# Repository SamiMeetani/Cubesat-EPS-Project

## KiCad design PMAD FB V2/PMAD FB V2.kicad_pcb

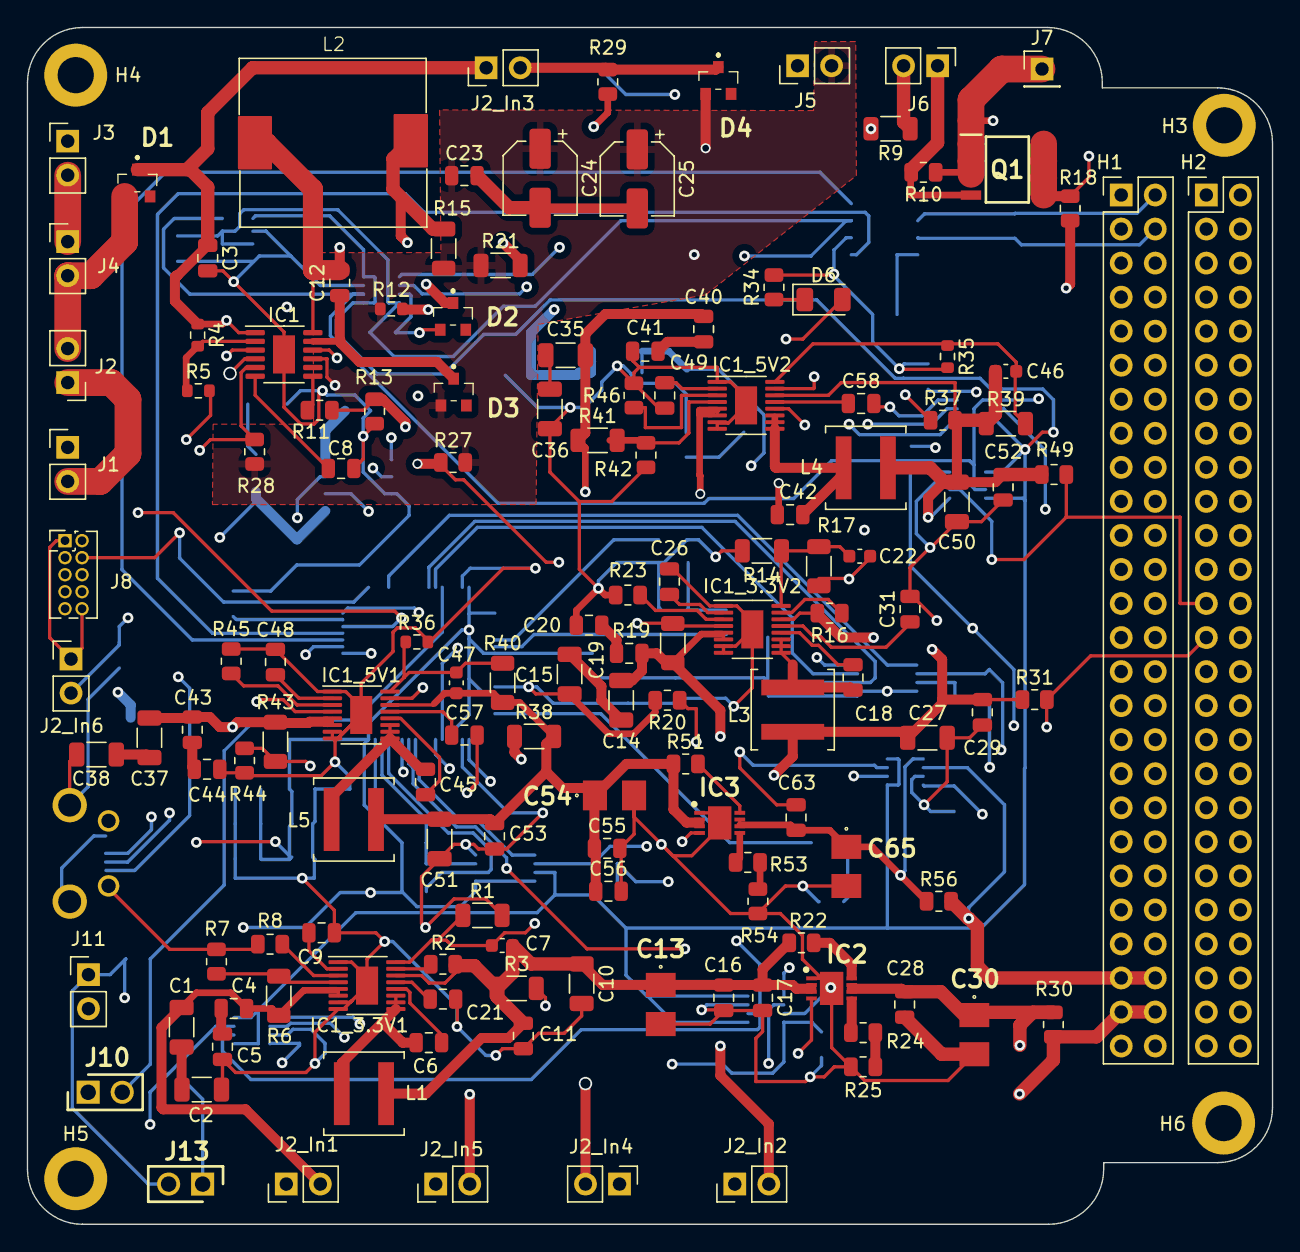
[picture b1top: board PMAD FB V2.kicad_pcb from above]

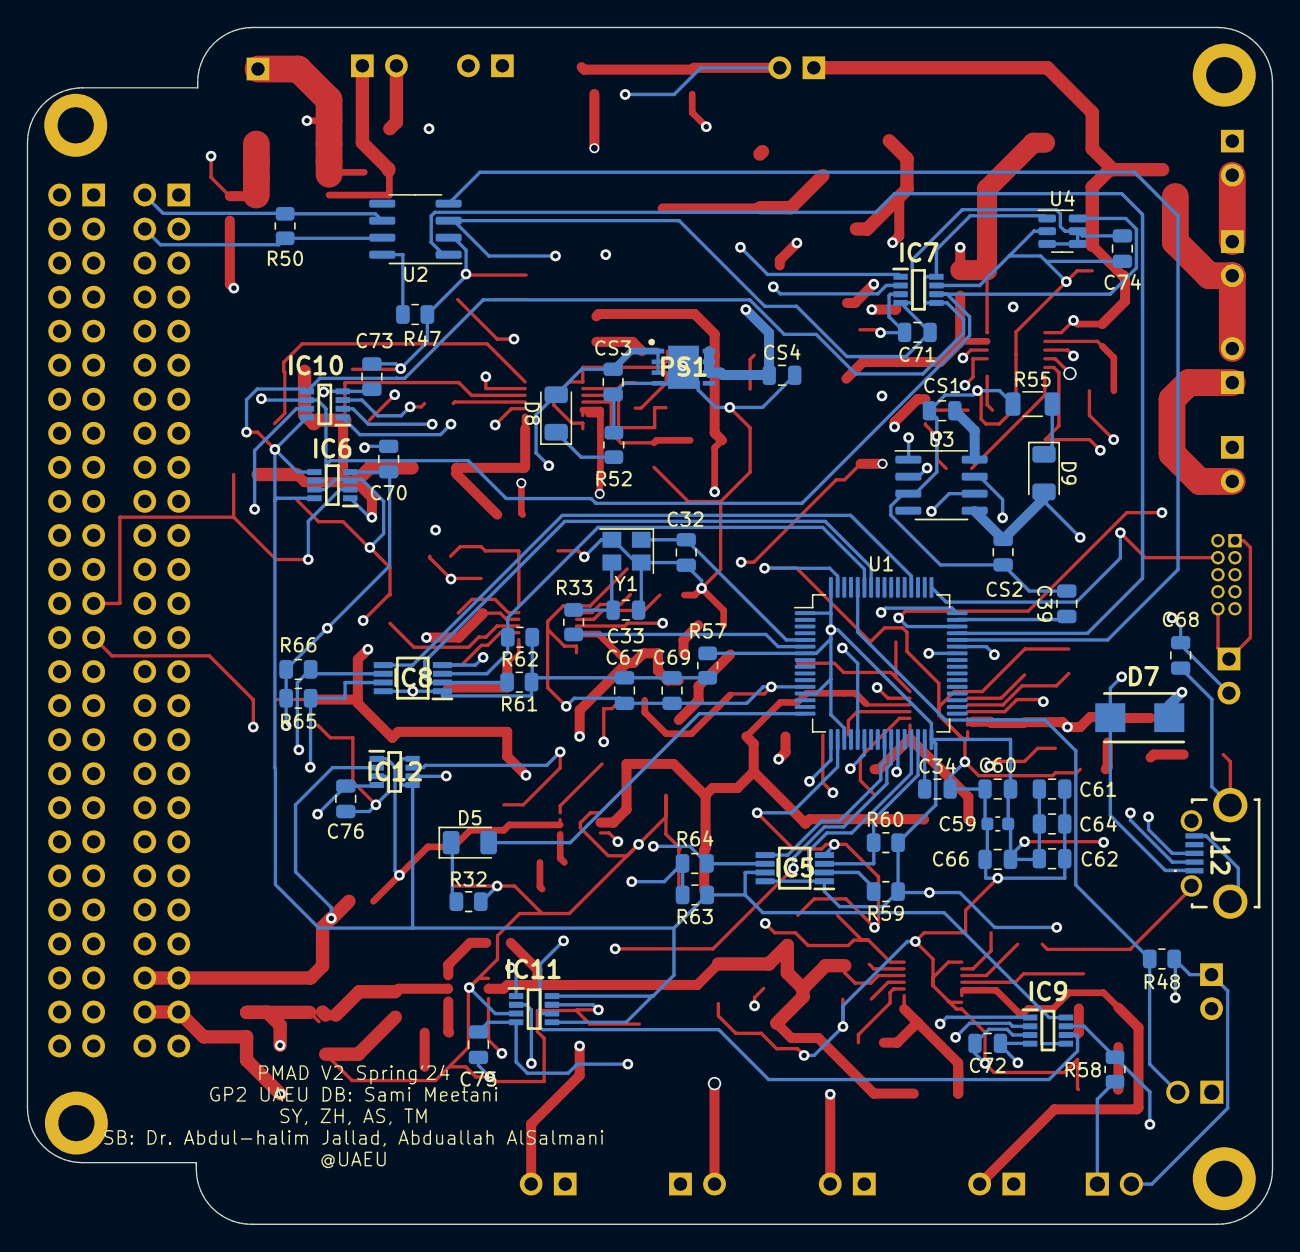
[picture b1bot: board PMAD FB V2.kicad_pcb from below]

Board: 4 copper layers, 92.9 x 89.3 mm, 205 parts (60 on the bottom side), 123 nets.

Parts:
C1, C2, C14, C15, C35, C36, C37, C38: 4.7uF; C_1206_3216Metric
C3, C23: 10uF; C_0805_2012Metric
C4, C5, C6, C9, C18, C19, C20, C26, C40, C41, C42, C43, C44, C45, C48, C49: 0.1uF; C_0805_2012Metric
C7, C22, C46, C47: 4.7pF; C_0603_1608Metric
C8, C11, C12, C21, C29, C31, C52, C53, C57, C58: 1uF; C_0805_2012Metric
C10, C27, C50, C51: 47uF; C_1206_3216Metric
C13, C30, C54, C65: T490B157M010ATE500; T490B
C16, C55: 10u; C_0805_2012Metric
C17, C28, C56, C63: 0.1u; C_0805_2012Metric
C24, C25: 47uF; CP_Elec_5x5.4
C32, C33: 12p; C_0805_2012Metric
C34, C39: 2u2; C_0805_2012Metric
C59: 4.7u; C_0603_1608Metric
C60, C61, C62, C64, C66, C68, C69, C70, C71, C72, C73, C74, C75, C76: 100n; C_0805_2012Metric
C67: 1u; C_0805_2012Metric
CS1, CS2: 100nF; C_0805_2012Metric
CS3, CS4: 10uF; C_0805_2012Metric
D1, D2, D3, D4: ZLLS500QTA
D5, D6: BLUE; LED_1206_3216Metric
D7: SD103AWS; DIOM5336X250N
D8, D9: LED; LED_1206_3216Metric
H1, H2: Conn_02x26_Odd_Even; PinHeader_2x26_P2.54mm_Vertical
H3, H4, H5, H6: MountingHole_Pad; MountingHole_2.7mm_M2.5_DIN965_Pad
IC1: LT3652HVEMSE#PBF; MSOP-12-1EP_3x4mm_P0.65mm_EP1.65x2.85mm
IC1_3.3V1, IC1_3.3V2, IC1_5V1, IC1_5V2: LT8610; MSOP-16-1EP_3x4.039mm_P0.5mm_EP1.651x2.845mm
IC2, IC3: TPS2557DRBR; SON50P300X300X80-9N-D
IC5, IC8: PCA9517ADP,118; SOP65P490X110-8N
IC6, IC7, IC9, IC10, IC11, IC12: INA219AIDCNR; SOP65P280X145-8N
J1, J2, J2_In1, J2_In2, J2_In3, J2_In4, J2_In5, J2_In6, J3, J4, J5, J6, J11: Conn_01x02; PinHeader_1x02_P2.54mm_Vertical
J7: Conn_01x01; PinHeader_1x01_P2.54mm_Vertical
J8: SWD; PinHeader_2x05_P1.27mm_Vertical
J10, J13: M20-9990246; HDRV2W66P0X254_1X2_508X254X874P
J12: U254-051T-4BHJ25-F2S; U254051T4BHJ25F2S
L1, L3, L4, L5: 2.2uH; L_Coilcraft_XAL5030-XXX
L2: 68uH; SLO1365H680MTT
PS1: LD39200DPUR; SON80P400X400X100-9N-D
Q1: FDS6630A; SOIC127P600X175-8N
R1, R14: 412k; R_1206_3216Metric
R2, R16, R37: 49.9k; R_0805_2012Metric
R3, R6, R9, R17, R19, R39, R40, R41, R43: 1M; R_1206_3216Metric
R4, R12: 47k; R_0603_1608Metric
R5: 65k; R_0603_1608Metric
R7, R20, R42, R44: 150k; R_0805_2012Metric
R8, R23, R45, R46: 18.2k; R_0805_2012Metric
R10, R59, R60, R61, R62, R63, R64, R65, R66: 4.7k; R_0805_2012Metric
R11, R13: 220k; R_0805_2012Metric
R15, R21: 0.1; R_1206_3216Metric
R18, R29, R30, R31, R49, R56: 0.01; R_0805_2012Metric
R22, R47, R51: 10K; R_0805_2012Metric
R24, R25, R53, R54: 20K; R_0805_2012Metric
R27, R28: 10k; R_0805_2012Metric
R32, R34: 1.5K; R_0805_2012Metric
R33: 47; R_0805_2012Metric
R35, R36: 243k; R_0603_1608Metric
R38: 49.9k; R_1206_3216Metric
R48, R58: 4.7K; R_0805_2012Metric
R50: 120; R_0805_2012Metric
R52: 240; R_0805_2012Metric
R55: 560; R_1206_3216Metric
R57: 0K; R_0805_2012Metric
U1: STM32F405RGTx; LQFP-64_10x10mm_P0.5mm
U2: SN65HVD230; SOIC-8_3.9x4.9mm_P1.27mm
U3: otter:CH330N; SOIC-8_3.9x4.9mm_P1.27mm
U4: TMP100; SOT-23-6
Y1: 16MHz; Crystal_SMD_3225-4Pin_3.2x2.5mm

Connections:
3.3V_PR_Output: H2.27, IC11.2 (IN-), R31.2
3.3V_SW: C7.2, C10.1, C11.1, C13.1 (+), C16.1, C17.1, IC1_3.3V1.14 (BIAS), IC2.2 (IN_1), IC2.3 (IN_2), L1.2, R2.2, R3.1, R22.1
3V3_SWT_OUTPUT: H1.49, H1.50, IC9.2 (IN-), R30.2
5V_PR_Output: H2.25, IC6.2 (IN-), R49.2
5V_SW: C47.2, C51.1, C53.1, C54.1 (+), C55.1, C56.1, IC1_5V1.14 (BIAS), IC3.2 (IN_1), IC3.3 (IN_2), L5.2, R38.2, R40.1, R51.1
5V_SWT_OUTPUT: H1.47, H1.48, IC12.2 (IN-), R56.2
+5V: CS4.1, D7.1 (K), PS1.6 (EN), PS1.7 (IN_1), PS1.8 (IN_2)
BIAS_P_3.3: C22.2, C27.1, C29.1, C68.1, IC1_3.3V2.14 (BIAS), IC11.1 (IN+), J2_In6.2, L3.2, R16.2, R17.1, R31.1
BIAS_P_5: C46.2, C50.1, C52.1, IC1_5V2.14 (BIAS), IC6.1 (IN+), L4.2, R37.2, R39.1, R49.1
BOOT0: J10.2, R48.2, U1.60 (BOOT0)
BST_P_3.3: C18.1, IC1_3.3V2.12 (BST)
BST_P_5: C42.1, IC1_5V2.12 (BST)
BST_S_3.3: C6.1, IC1_3.3V1.12 (BST)
BST_S_5: C45.1, IC1_5V1.12 (BST)
CAN1_RX: U1.44 (PA11), U2.4 (R)
CAN1_TX: U1.45 (PA12), U2.1 (D)
CANH1: H1.4, R50.1, U2.7 (CANH)
CANL1: H1.2, R50.2, U2.6 (CANL)
CHRG: IC1.4 (~CHRG), R27.1, U1.22 (PA6)
ENABLE_3v3_SW: IC2.4 (EN), U1.26 (PB0)
ENABLE_5v_SW: IC3.4 (EN), U1.27 (PB1)
EN/UV_P_3.3: IC1_3.3V2.4 (EN/UV), R19.2, R20.1
EN/UV_P_5: IC1_5V2.4 (EN/UV), R41.2, R42.1
EN/UV_S_3.3: IC1_3.3V1.4 (EN/UV), R6.2, R7.1
EN/UV_S_5: IC1_5V1.4 (EN/UV), R43.2, R44.1
FAULT: IC1.5 (~FAULT), R28.1, U1.21 (PA5)
FB_P_3.3: C22.1, IC1_3.3V2.16 (FB), R14.1, R17.2
FB_P_5: C46.1, IC1_5V2.16 (FB), R35.1, R39.2
FB_S_3.3: C7.1, IC1_3.3V1.16 (FB), R1.1, R3.2
FB_S_5: C47.1, IC1_5V1.16 (FB), R36.1, R40.2
GND: C2.2, C3.2, C5.2, C8.2, C9.1, C10.2, C11.2, C13.2 (-), C15.2, C16.2, C17.2, C20.2, C21.2, C26.1, C27.2, C28.2, C29.2, C30.2 (-), C31.2, C32.2, C33.2, C34.2, C36.2, C38.2, C39.2, C41.2, C44.2, C48.1, C49.1, C50.2, C51.2, C52.2, C53.2, C54.2 (-), C55.2, C56.2, C57.2, C58.2, C59.2, C60.2, C61.2, C62.2, C63.2, C64.2, C65.2 (-), C66.2, C67.2, C68.2, C69.2, C70.2, C71.2, C72.2, C73.2, C74.2, C75.2, C76.2, CS1.2, CS2.2, CS3.2, CS4.2, D2.3 (A), H2.29, H2.30, H2.32, H2.48, H2.52, H3.1, H4.1, H5.1, H6.1, IC1.13 (GND), IC1_3.3V1.1 (SYNC), IC1_3.3V1.7 (PGND_1), IC1_3.3V1.8 (PGND_2), IC1_3.3V1.17 (EP), IC1_3.3V2.1 (SYNC), IC1_3.3V2.7 (PGND_1), IC1_3.3V2.8 (PGND_2), IC1_3.3V2.17 (EP), IC1_5V1.1 (SYNC), IC1_5V1.7 (PGND_1), IC1_5V1.8 (PGND_2), IC1_5V1.17 (EP), IC1_5V2.1 (SYNC), IC1_5V2.7 (PGND_1), IC1_5V2.8 (PGND_2), IC1_5V2.17 (EP), IC2.1 (GND), IC2.9 (EP), IC3.1 (GND), IC3.9 (EP), IC5.4 (GND), IC6.3 (GND), IC6.7 (A0), IC7.3 (GND), IC7.7 (A0), IC8.4 (GND), IC9.3 (GND), IC9.7 (A0), IC10.3 (GND), IC10.7 (A0), IC11.3 (GND), IC11.7 (A0), IC12.3 (GND), IC12.7 (A0), J1.1, J3.1, J5.1, J8.3, J8.5, J8.9, J10.1, J12.5, J12.MH1, J12.MH2, J12.MH3, J12.MH4, PS1.4 (GND_1), PS1.9 (GND_2), R1.2, R5.2, R7.2, R8.2, R9.2, R13.2, R14.2, R20.2, R23.2, R25.2, R32.2, R34.2, R35.2, R36.2, R42.2, R44.2, R45.2, R46.2, R47.1, R52.1, R54.2, R55.1, R58.2, U1.12 (VSSA), U1.18 (VSS), U1.63 (VSS), U2.2 (GND), U3.3 (GND), U4.2 (GND), Y1.2, Y1.4
HSE_IN: C32.1, U1.5 (PH0), Y1.1
HSE_OUT: R33.1, U1.6 (PH1)
I2C1_EN: IC8.5 (EN), U1.52 (PC11)
I2C1_SCL: IC8.2 (SCLA), R61.2, U1.58 (PB6)
I2C1_SCL_BUS: H1.43, IC8.7 (SCLB), R65.2
I2C1_SDA: IC8.3 (SDAA), R62.2, U1.59 (PB7)
I2C1_SDA_BUS: H1.41, IC8.6 (SDAB), R66.2
I2C2_EN: IC5.5 (EN), U1.25 (PC5)
I2C2_SCL: IC5.2 (SCLA), R59.2, U1.29 (PB10)
I2C2_SCL_BUS: IC5.7 (SCLB), IC6.5 (SCL), IC6.8 (A1), IC7.5 (SCL), IC7.8 (A1), IC9.5 (SCL), IC9.8 (A1), IC10.5 (SCL), IC10.8 (A1), IC11.5 (SCL), IC11.8 (A1), IC12.5 (SCL), IC12.8 (A1), R63.2, U4.1 (SCL)
I2C2_SDA: IC5.3 (SDAA), R60.2, U1.30 (PB11)
I2C2_SDA_BUS: IC5.6 (SDAB), IC6.6 (SDA), IC7.6 (SDA), IC9.6 (SDA), IC10.6 (SDA), IC11.6 (SDA), IC12.6 (SDA), R64.2, U4.6 (SDA)
KS_OUTPUT: IC10.2 (IN-), J2_In1.1, J2_In2.1, J2_In4.1, J2_In5.1, R18.2
LED_STATUS: D5.2 (A), U1.16 (PA2)
LED_STATUS_1: D6.2 (A), U1.17 (PA3)
NRST: C59.1, C60.1, C61.1, C62.1, C64.1, C66.1, C67.1, C69.1, C70.1, C71.1, C72.1, C73.1, C74.1, C75.1, C76.1, IC5.1 (VCC(A)), IC5.8 (VCC(B)), IC6.4 (VS), IC7.4 (VS), IC8.1 (VCC(A)), IC8.8 (VCC(B)), IC9.4 (VS), IC10.4 (VS), IC11.4 (VS), IC12.4 (VS), J2_In6.1, J8.1, J8.10, J11.1, J13.2, R48.1, R57.1, R57.2, R59.1, R60.1, R61.1, R62.1, R63.1, R64.1, R65.1, R66.1, U1.1 (VBAT), U1.7 (NRST), U1.13 (VDDA), U1.19 (VDD), U1.32 (VDD), U1.48 (VDD), U1.64 (VDD), U2.3 (VCC), U4.3 (ADD1), U4.4 (V+), U4.5 (ADD0)
unnamed: C1.2, C2.1
unnamed: C4.2, C5.1
unnamed: C14.2, C15.1
unnamed: C19.2, C20.1
unnamed: C23.2, C24.2, C25.2
unnamed: C33.1, R33.2, Y1.3
unnamed: C35.2, C36.1
unnamed: C37.2, C38.1
unnamed: C40.2, C41.1
unnamed: C43.2, C44.1
unnamed: C3.1, D1.1 (K), IC1.1 (VIN), IC1.3 (~SHDN), J2_In3.1, R4.1
unnamed: C12.2, D2.1 (K), IC1.12 (SW), L2.1
unnamed: C12.1, D3.1 (K), IC1.11 (BOOST)
unnamed: D5.1 (K), R32.1
unnamed: D6.1 (K), R34.1
unnamed: CS2.1, D7.2 (A), D9.2 (A), J12.1, U3.5 (VCC)
unnamed: CS3.1, D8.2 (A), J11.2, PS1.1 (OUT_1), PS1.2 (OUT_2), PS1.3 (ADJ/SENSE)
unnamed: D8.1 (K), R52.2
unnamed: D9.1 (K), R55.2
unnamed: IC1.10 (SENSE), L2.2, R15.1, R21.2
unnamed: C8.1, IC1.6 (TIMER)
unnamed: IC1.7 (VFB), R11.1
unnamed: IC1.2 (VIN_REG), R4.2, R5.1
unnamed: C21.1, IC1_3.3V1.13 (INTVCC)
unnamed: IC1_3.3V1.3 (RT), R8.1
unnamed: C9.2, IC1_3.3V1.2 (TR/SS)
unnamed: C31.1, IC1_3.3V2.13 (INTVCC)
unnamed: IC1_3.3V2.3 (RT), R23.1
unnamed: C26.2, IC1_3.3V2.2 (TR/SS)
unnamed: C57.1, IC1_5V1.13 (INTVCC)
unnamed: IC1_5V1.3 (RT), R45.1
unnamed: C48.2, IC1_5V1.2 (TR/SS)
unnamed: C58.1, IC1_5V2.13 (INTVCC)
unnamed: IC1_5V2.3 (RT), R46.1
unnamed: C49.2, IC1_5V2.2 (TR/SS)
unnamed: IC2.5 (ILIM), R24.1
unnamed: IC2.8 (~FAULT), R22.2
unnamed: IC3.5 (ILIM), R53.1
unnamed: IC3.8 (~FAULT), R51.2
unnamed: J1.2, J2.1
unnamed: J3.2, J4.1
unnamed: J6.1, Q1.4 (G), R10.2
unnamed: J6.2, R9.1
unnamed: J13.1, R58.1
unnamed: R11.2, R12.2, R13.1
unnamed: R24.2, R25.1
unnamed: R53.2, R54.1
unnamed: C34.1, U1.31 (VCAP_1)
unnamed: C39.1, U1.47 (VCAP_2)
unnamed: R47.2, U2.8 (Rs)
unnamed: J12.3, U3.1 (UD+)
unnamed: J12.2, U3.2 (UD-)
unnamed: CS1.1, U3.8 (V3)
PG_P_3.3: IC1_3.3V2.15 (PG), R16.1
PG_P_5: IC1_5V2.15 (PG), R37.1
PG_S_3.3: IC1_3.3V1.15 (PG), R2.1
PG_S_5: IC1_5V1.15 (PG), R38.1
PV_cells_input: D1.3 (A), J2.2, J4.2
SWCLK: J8.4, U1.49 (PA14)
SWDIO: J8.2, U1.46 (PA13)
SW_1_P_3.3: C18.2, IC1_3.3V2.9 (SW_1), IC1_3.3V2.10 (SW_2), IC1_3.3V2.11 (SW_3), L3.1
SW_1_P_5: C42.2, IC1_5V2.9 (SW_1), IC1_5V2.10 (SW_2), IC1_5V2.11 (SW_3), L4.1
SW_1_S_3.3: C6.2, IC1_3.3V1.9 (SW_1), IC1_3.3V1.10 (SW_2), IC1_3.3V1.11 (SW_3), L1.1
SW_1_S_5: C45.2, IC1_5V1.9 (SW_1), IC1_5V1.10 (SW_2), IC1_5V1.11 (SW_3), L5.1
System_Input: IC7.1 (IN+), J7.1, Q1.1 (S_1), Q1.2 (S_2), Q1.3 (S_3), R10.1, R29.1
USART1_RX: U1.43 (PA10), U3.6 (TXD)
USART1_TX: U1.42 (PA9), U3.7 (RXD)
VBATT: C23.1, C24.1, C25.1, D3.3 (A), D4.3 (A), H2.45, H2.46, IC1.9 (BAT), J5.2, R12.1, R15.2, R21.1, R27.2, R28.2
VIN1+: IC10.1 (IN+), Q1.5 (D_1), Q1.6 (D_2), Q1.7 (D_3), Q1.8 (D_4), R18.1
VIN4+: C28.1, C30.1 (+), IC2.6 (OUT_1), IC2.7 (OUT_2), IC9.1 (IN+), R30.1
VIN5+: C63.1, C65.1 (+), IC3.6 (OUT_1), IC3.7 (OUT_2), IC12.1 (IN+), R56.1
VIN-: D4.1 (K), IC7.2 (IN-), J2_In3.2, R29.2
VIN_P_3.3: C14.1, C19.1, IC1_3.3V2.5 (VIN_1), IC1_3.3V2.6 (VIN_2), J2_In2.2, R19.1
VIN_P_5: C35.1, C40.1, IC1_5V2.5 (VIN_1), IC1_5V2.6 (VIN_2), J2_In4.2, R41.1
VIN_S_3.3: C1.1, C4.1, IC1_3.3V1.5 (VIN_1), IC1_3.3V1.6 (VIN_2), J2_In1.2, R6.1
VIN_S_5: C37.1, C43.1, IC1_5V1.5 (VIN_1), IC1_5V1.6 (VIN_2), J2_In5.2, R43.1

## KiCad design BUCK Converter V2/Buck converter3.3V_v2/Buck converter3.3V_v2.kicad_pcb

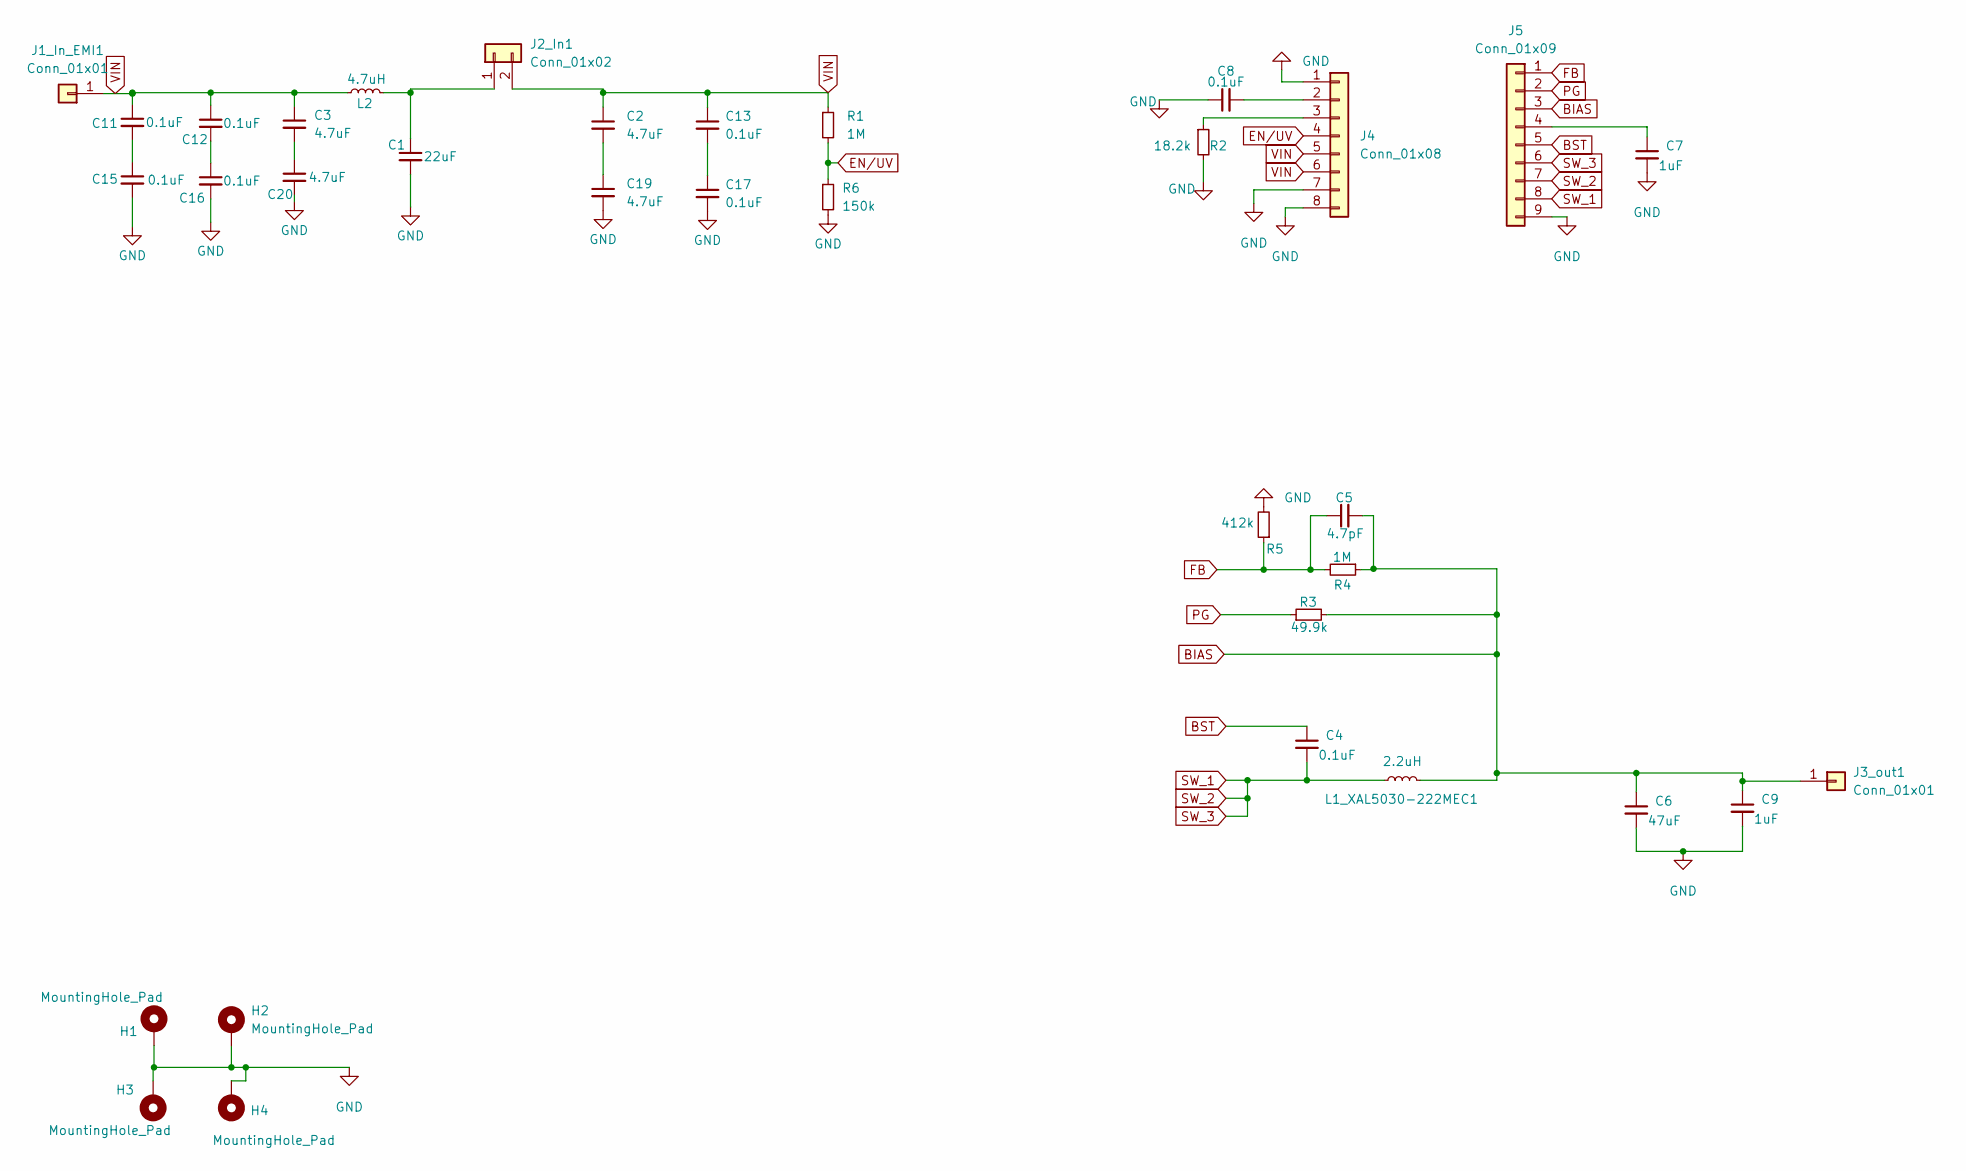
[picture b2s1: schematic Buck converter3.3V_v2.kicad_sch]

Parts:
C1: 22uF; CP_Elec_6.3x7.7
C2, C3, C19, C20: 4.7uF; C_1206_3216Metric
C4, C8, C11, C12, C13, C15, C16, C17: 0.1uF; C_0805_2012Metric
C5: 4.7pF; C_0805_2012Metric
C6: 47uF; C_1210_3225Metric
C7: 1uF; L_0805_2012Metric
C9: 1uF; C_0805_2012Metric
H1, H2, H3, H4: MountingHole_Pad; MountingHole_2.2mm_M2_Pad
J1_In_EMI1, J3_out1: Conn_01x01; PinHeader_1x01_P2.54mm_Vertical
J2_In1: Conn_01x02; PinHeader_1x02_P2.54mm_Vertical
J4: Conn_01x08; PinHeader_1x08_P2.54mm_Vertical
J5: Conn_01x09; PinHeader_1x09_P2.54mm_Vertical
L1_XAL5030-222MEC1: 2.2uH; L_Sunlord_MWSA0518_5.4x5.2mm
L2: 4.7uH; L_Vishay_IHLP-2525
R1, R4: 1M; R_0805_2012Metric
R2: 18.2k; R_0805_2012Metric
R3: 49.9k; R_0805_2012Metric
R5: 412k; C_0805_2012Metric
R6: 150k; R_0805_2012Metric

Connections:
BIAS: C5.2, C6.1, C9.1, J3_out1.1, J5.3, L1_XAL5030-222MEC1.2, R3.2, R4.1
BST: C4.1, J5.5
EN/UV: J4.4, R1.2, R6.1
FB: C5.1, J5.1, R4.2, R5.1
GND: C1.2, C6.2, C7.2, C8.1, C9.2, C15.2, C16.2, C17.2, C19.2, C20.2, H1.1, H2.1, H3.1, H4.1, J4.1, J4.7, J4.8, J5.9, R2.2, R5.2, R6.2
unnamed: C1.1, J2_In1.1, L2.2
unnamed: C7.1, J5.4
unnamed: C8.2, J4.2
unnamed: C11.2, C15.1
unnamed: C12.2, C16.1
unnamed: C13.2, C17.1
unnamed: C2.2, C19.1
unnamed: C3.2, C20.1
unnamed: J4.3, R2.1
PG: J5.2, R3.1
SW_1: C4.2, J5.6, J5.7, J5.8, L1_XAL5030-222MEC1.1
VIN: C2.1, C3.1, C11.1, C12.1, C13.1, J1_In_EMI1.1, J2_In1.2, J4.5, J4.6, L2.1, R1.1

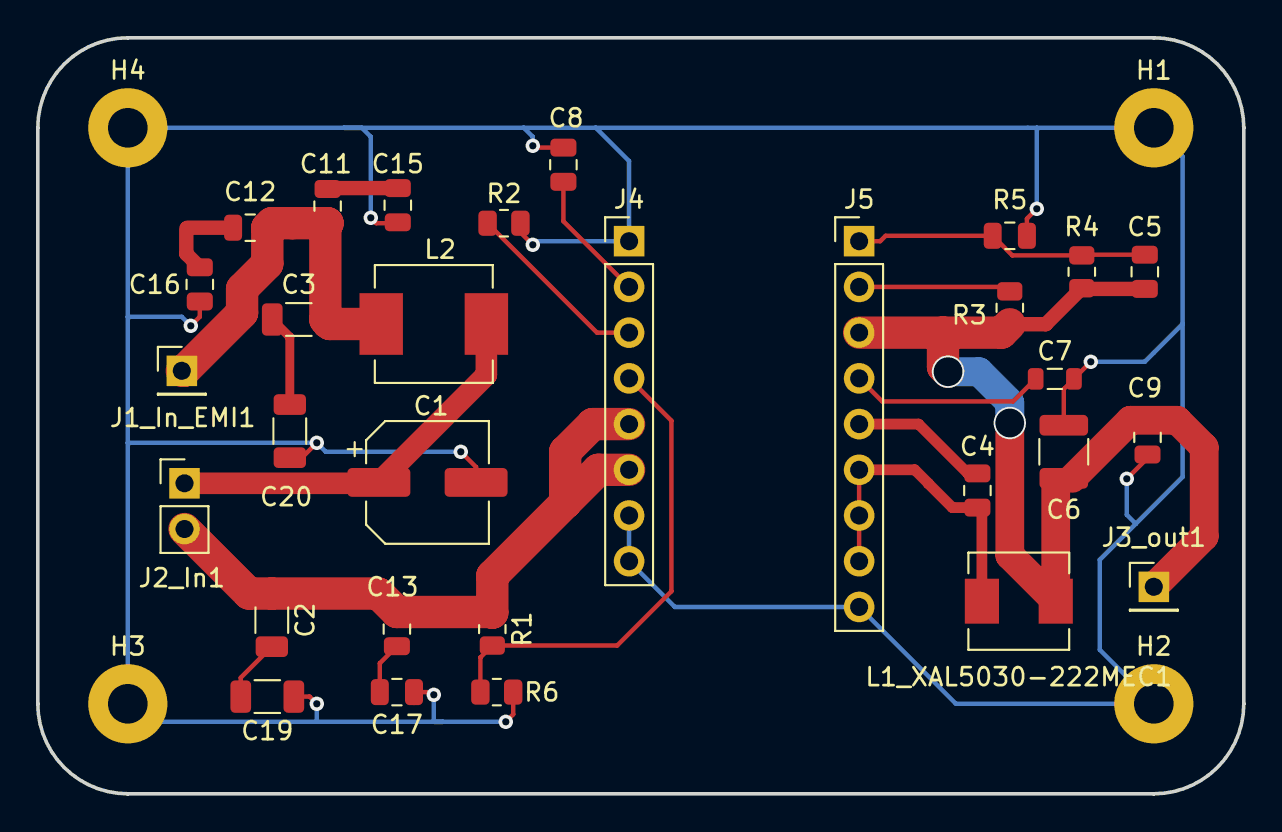
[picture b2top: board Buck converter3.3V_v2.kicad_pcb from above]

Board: 2 copper layers, 67.0 x 42.0 mm, 34 parts (0 on the bottom side), 17 nets.
